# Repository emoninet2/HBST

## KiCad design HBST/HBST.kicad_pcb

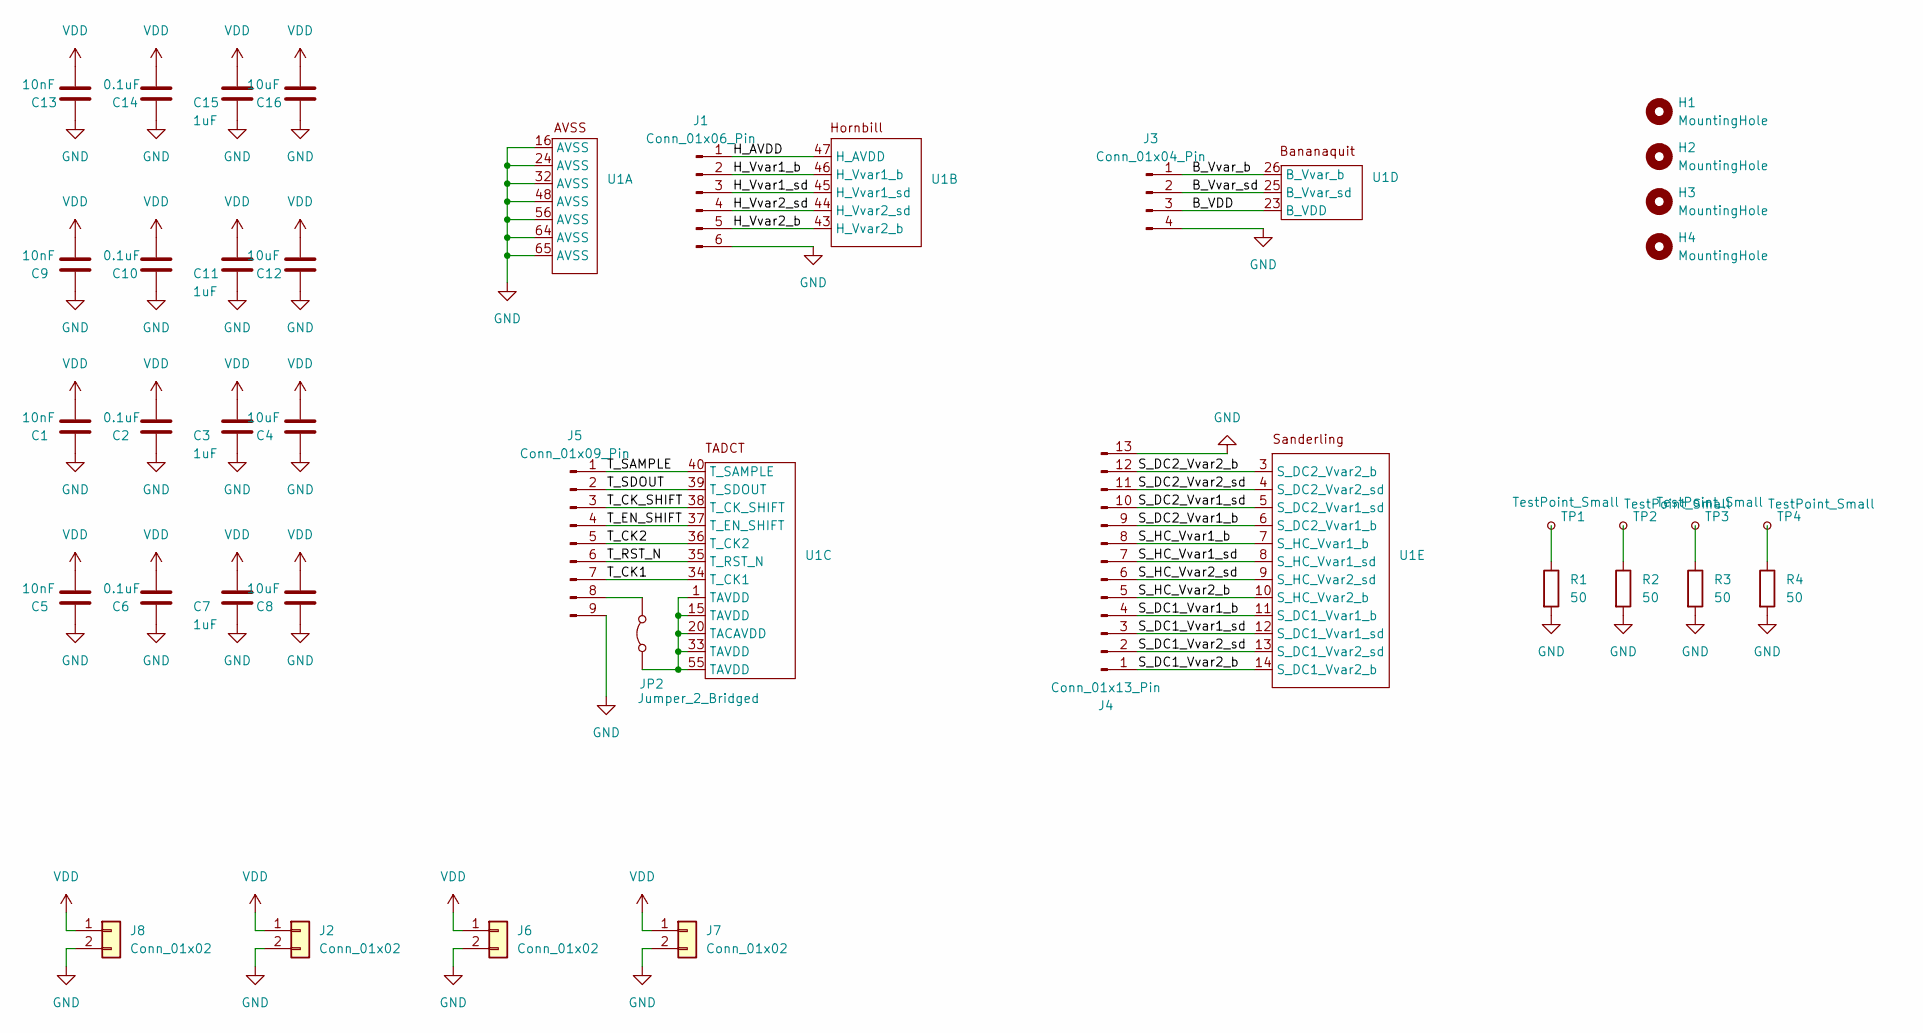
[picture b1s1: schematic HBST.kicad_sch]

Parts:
C1, C5, C9, C13: 10nF; C_0805_2012Metric; Manufacturer_Part_Number CL21B103KBANNNC; LCSC C1710
C2, C6, C10, C14: 0.1uF; C_0805_2012Metric; Manufacturer_Part_Number CL21B104KBCNNNC; LCSC C1711
C3, C7, C11, C15: 1uF; C_0805_2012Metric; Manufacturer_Part_Number CL21B105KAFNNNE; LCSC C116352
C4, C8, C12, C16: 10uF; C_0805_2012Metric; Manufacturer_Part_Number CL21A106KOQNNNE; LCSC C1713
H1, H2, H3, H4: MountingHole; MountingHole_5mm_Pad_TopBottom
J1: Conn_01x06_Pin; PinHeader_1x06_P2.54mm_Horizontal
J2, J6, J7, J8: Conn_01x02; PinHeader_1x02_P2.54mm_Horizontal
J3: Conn_01x04_Pin; PinHeader_1x04_P2.54mm_Horizontal
J4: Conn_01x13_Pin; PinHeader_1x13_P2.54mm_Horizontal
J5: Conn_01x09_Pin; PinHeader_1x09_P2.54mm_Horizontal
JP2: Jumper_2_Bridged; TestPoint_2Pads_Pitch2.54mm_Drill0.8mm
R1, R2, R3, R4: 50; R_0805_2012Metric_Pad1.20x1.40mm_HandSolder
TP1, TP2, TP3, TP4: TestPoint_Small; TestPoint_Pad_D1.0mm
U1: QFN-64-1EP_9x9mm_P0.5mm_EP6x6mm

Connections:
/B_VDD: J3.3, U1.23 (B_VDD)
/B_Vvar_b: J3.1, U1.26 (B_Vvar_b)
/B_Vvar_sd: J3.2, U1.25 (B_Vvar_sd)
/H_AVDD: J1.1, U1.47 (H_AVDD)
/H_Vvar1_b: J1.2, U1.46 (H_Vvar1_b)
/H_Vvar1_sd: J1.3, U1.45 (H_Vvar1_sd)
/H_Vvar2_b: J1.5, U1.43 (H_Vvar2_b)
/H_Vvar2_sd: J1.4, U1.44 (H_Vvar2_sd)
/S_DC1_Vvar1_b: J4.4, U1.11 (S_DC1_Vvar1_b)
/S_DC1_Vvar1_sd: J4.3, U1.12 (S_DC1_Vvar1_sd)
/S_DC1_Vvar2_b: J4.1, U1.14 (S_DC1_Vvar2_b)
/S_DC1_Vvar2_sd: J4.2, U1.13 (S_DC1_Vvar2_sd)
/S_DC2_Vvar1_b: J4.9, U1.6 (S_DC2_Vvar1_b)
/S_DC2_Vvar1_sd: J4.10, U1.5 (S_DC2_Vvar1_sd)
/S_DC2_Vvar2_b: J4.12, U1.3 (S_DC2_Vvar2_b)
/S_DC2_Vvar2_sd: J4.11, U1.4 (S_DC2_Vvar2_sd)
/S_HC_Vvar1_b: J4.8, U1.7 (S_HC_Vvar1_b)
/S_HC_Vvar1_sd: J4.7, U1.8 (S_HC_Vvar1_sd)
/S_HC_Vvar2_b: J4.5, U1.10 (S_HC_Vvar2_b)
/S_HC_Vvar2_sd: J4.6, U1.9 (S_HC_Vvar2_sd)
/T_CK1: J5.7, U1.34 (T_CK1)
/T_CK2: J5.5, U1.36 (T_CK2)
/T_CK_SHIFT: J5.3, U1.38 (T_CK_SHIFT)
/T_EN_SHIFT: J5.4, U1.37 (T_EN_SHIFT)
/T_RST_N: J5.6, U1.35 (T_RST_N)
/T_SAMPLE: J5.1, U1.40 (T_SAMPLE)
/T_SDOUT: J5.2, U1.39 (T_SDOUT)
GND: C1.1, C2.1, C3.1, C4.1, C5.1, C6.1, C7.1, C8.1, C9.1, C10.1, C11.1, C12.1, C13.1, C14.1, C15.1, C16.1, J1.6, J2.2, J3.4, J4.13, J5.9, J6.2, J7.2, J8.2, R1.2, R2.2, R3.2, R4.2, U1.16 (AVSS), U1.24 (AVSS), U1.32 (AVSS), U1.48 (AVSS), U1.56 (AVSS), U1.64 (AVSS), U1.65 (AVSS)
unnamed: J5.8, JP2.2 (B)
unnamed: JP2.1 (A), U1.1 (TAVDD), U1.15 (TAVDD), U1.20 (TACAVDD), U1.33 (TAVDD), U1.55 (TAVDD)
unnamed: R1.1, TP1.1
unnamed: R2.1, TP2.1
unnamed: R3.1, TP3.1
unnamed: R4.1, TP4.1
VDD: C1.2, C2.2, C3.2, C4.2, C5.2, C6.2, C7.2, C8.2, C9.2, C10.2, C11.2, C12.2, C13.2, C14.2, C15.2, C16.2, J2.1, J6.1, J7.1, J8.1

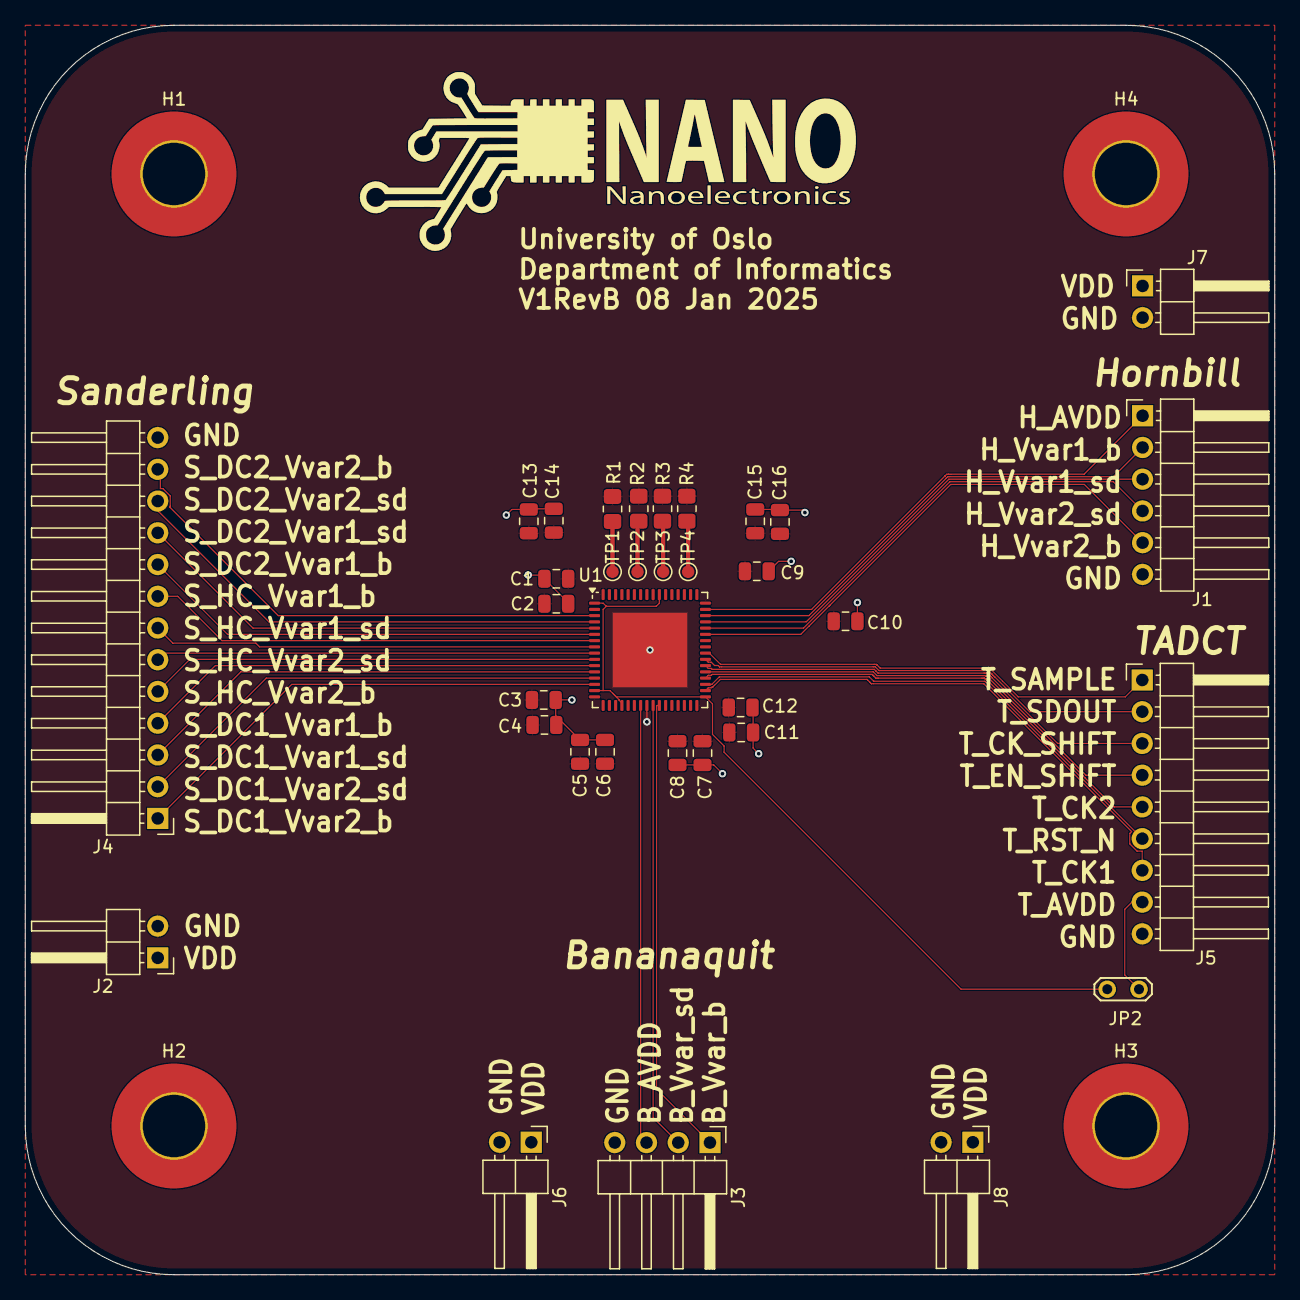
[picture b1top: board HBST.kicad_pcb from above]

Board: 13 copper layers, 100.0 x 100.0 mm, 38 parts (0 on the bottom side), 35 nets.

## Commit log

2024-08-20 added existing project
2024-09-12 updated design
2024-09-27 added decoupling capacitors and fixed copper fill zone on In2 copper layer
2024-09-27 minor update
2024-09-27 added description
2025-01-08 fixed to correct package and minor component placement changes
